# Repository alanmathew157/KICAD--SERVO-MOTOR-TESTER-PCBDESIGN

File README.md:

# SERVO MOTOR TESTER PCB Design using KICAD -ALTIMUM
## PCB TOP VIEW

## PCB BOTTOM VIEW

## Project Overview🔧
This servo tester circuit is designed to generate a controlled PWM (Pulse Width Modulation) signal to test and position a standard servo motor by producing periodic control pulses at approximately 50Hz, where the pulse width (typically between 1ms and 2ms) determines the angular position of the servo shaft; the circuit uses a timing configuration (such as a timer IC–based oscillator stage) to create stable pulses, and a potentiometer is used to vary the pulse width, allowing smooth manual adjustment of the servo position from minimum to maximum angle, while resistors and capacitors set the timing frequency and ensure signal stability; the output PWM signal is connected to the servo’s control pin, with proper 5V power and ground connections provided to drive the motor reliably. The circuit is tested by connecting a standard servo motor to the output, supplying 5V power, and rotating the potentiometer to observe smooth movement of the servo shaft across its range, confirming correct pulse generation and operation. This project is my attempt at learning KiCad and understanding how PWM-based servo control circuits are designed, tested, and implemented at the schematic level.

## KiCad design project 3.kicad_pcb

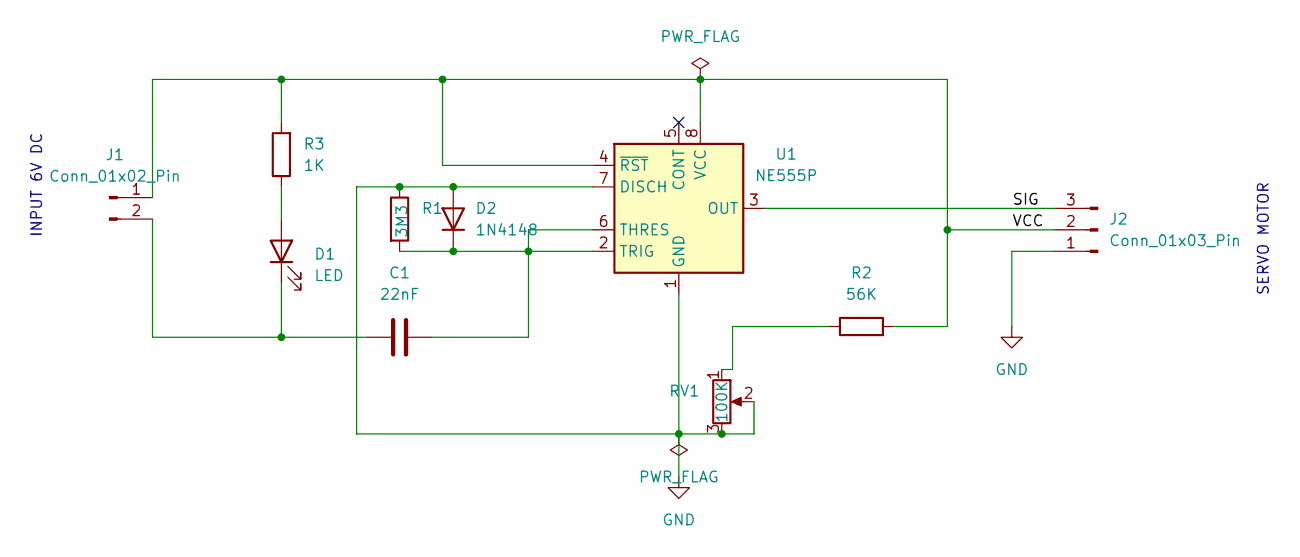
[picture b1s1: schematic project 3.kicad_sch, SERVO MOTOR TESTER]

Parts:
C1: 22nF; C_Disc_D4.3mm_W1.9mm_P5.00mm
D1: LED; LED_D3.0mm
D2: 1N4148; D_DO-35_SOD27_P7.62mm_Horizontal
J1: Conn_01x02_Pin; PinHeader_1x02_P2.54mm_Horizontal
J2: Conn_01x03_Pin; PinHeader_1x03_P2.54mm_Horizontal
R1: 3M3; R_Axial_DIN0204_L3.6mm_D1.6mm_P7.62mm_Horizontal
R2: 56K; R_Axial_DIN0204_L3.6mm_D1.6mm_P7.62mm_Horizontal
R3: 1K; R_Axial_DIN0204_L3.6mm_D1.6mm_P7.62mm_Horizontal
RV1: 100K; Potentiometer_Alps_RK163_Single_Horizontal
U1: NE555P; DIP-8_W7.62mm

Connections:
/SIG: J2.3, U1.3 (OUT)
/VCC: J1.1, J2.2, R2.2, R3.2, U1.4 (~RST), U1.8 (VCC)
GND: D2.2 (A), J2.1, R1.1, RV1.2, RV1.3, U1.1 (GND), U1.7 (DISCH)
unnamed: D1.2 (A), R3.1
unnamed: C1.1, D1.1 (K), J1.2
unnamed: C1.2, D2.1 (K), R1.2, U1.2 (TRIG), U1.6 (THRES)
unnamed: R2.1, RV1.1

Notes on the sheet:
SERVO MOTOR
INPUT 6V DC

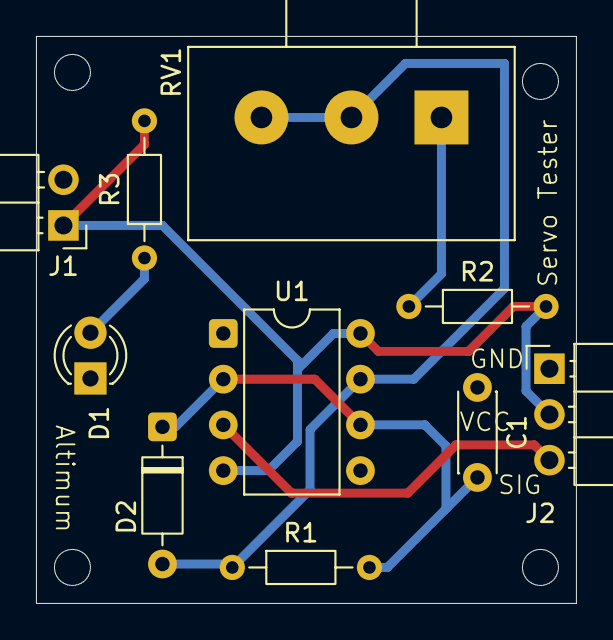
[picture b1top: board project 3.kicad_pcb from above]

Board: 2 copper layers, 30.0 x 31.5 mm, 10 parts (0 on the bottom side), 7 nets.

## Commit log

2026-03-03 Add README for SERVO MOTOR TESTER PCB Design
    Added project overview and images for PCB design.
